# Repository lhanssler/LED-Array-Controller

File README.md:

**LED-Array-Controller**

**Part A: Repository Contents**
1. telemetrix_controller.py: Python module created to interact with the Arduino
    Nano. Allows the Nano to connect to a PCA9685 driver and flash LEDs.
    This module is the only required import. Other files are dependencies.
2. telemetrix: Python package which can be imported to control an Arduino
    using Python over a serial connection. This package is a dependency of
    telemetrix_controller.py and telemetrix_pca9685.
3. telemetrix_pca9685: Python package which can be imported to connect with an
    Arduino and PCA9685 driver. The package uses telemetrix for the Arduino
    connection and is a dependency of telemetrix_controller.py. The package
    was sourced from: https://github.com/MrYsLab/telemetrix-extensions
4. Telemetrix4Arduino: Folder containing Telemetrix4Arduino.ino, the Arduino
    sketch file which must be opened in the Arduino IDE and uploaded to the
    Arduino Nano before the connection from Python is established. ino files
    can only be opened in the Arduino IDE if they are located in a folder
    of the same name, which is why the folder is provided.
5. warm_test.txt: A text file is used to configure the LED array controller
    when the telemetrix_controller.py module is utilized. This is the text
    file used for the January 2025 warm test in the LL130 cryostat and can be
    referenced as an example. The file is explained in more detail in Part C of
    the README.md.
6. serial: Python's serial library, a dependency of telemetrix. serial is
    should already be installed on the host device, but some devices running
    older versions of Python have issues when telemetrix calls certain functions
    from serial. This version of serial has been shown to function properly.
7. KiCad Files: Folder containing the KiCad files for LED Array Controller PCBs.
    Revisions 3 and 4 of the board are in the folder, which includes their
    schematics and board diagrams. KiCad Files has its own README file in
    the folder.
8. README.md: This README file.

**Part B: Repository Dependencies**
1. Arduino IDE: Download at this link: https://www.arduino.cc/en/software
2. Telemetrix4Arduino: Arduino library. Download instructions:
    In the Arduino IDE, select Tools -> Manage Libraries and search for
    Telemetrix4Arduino. Install the library and its dependencies.
3. Telemetrix4Arduino.ino, Arduino sketch: File to be uploaded to the Arduino
    Nano to begin the serial connection. This is the Telemetrix4Arduino library
    example file.
4. telemetrix, telemetrix_pca9685, serial: Python packages included in this
    repository which are dependencies of the telemetrix_controller.py file.
5. Configuration text file: The text file which defines the LED Array PCB's
    connection to the LED Array Controller PCB.

**Part C: Instructions for Using telemetrix_controller**
1. Create the configuration file: This is the text file, with warm_test.txt as
    an example. Each row represents an Arduino Nano pin or PCA9685 driver
    channel to be used for the LED array. Each row has 3 columns delimited by a
    single space. The first column is the row or column number (1-indexed) of
    the LED array which the pin/channel corresponds to. The second column is
    the digital pin or channel number. The third number is the driver address.
    If the text row corresponds to a Nano pin, then the driver address should
    be entered as 0. The default driver address is 64 (or 0x40), which
    corresponds to none of the solder jumpers being connected on the LED Array
    Controller PCB.
2. In the Arduino IDE, upload the Telemetrix4Arduino.ino file to the Arduino
    Nano.
3. In Python, import telemetrix_controller. No other explicit imports are
    required for repository use.
4. In Python, create an object from the telemetrix_controller.Arduino class. The
    constructor only has one argument, which is required: the string indicating
    the filepath to the configuration file.
5. The object's methods can now be called to control the LED array.
    Please refer to the docstrings in telemetrix_controller.py for further
    instructions on use.

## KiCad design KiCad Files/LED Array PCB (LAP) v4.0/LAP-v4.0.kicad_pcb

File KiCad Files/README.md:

**KiCad Files**

The KiCad Files folder contains the two most recent revisions of the LED Array
PCB (LAP): v3.0 and v4.0.

The telemetrix_controller module was designed with v3.0 in mind, and v3.0 is
the version that is printed and populated in LL113. v3.0 contains:
- An Arduino Nano (used with header pins), PCA9685 IC which is SMT soldered
    directly to the board.
- A through-hole D-sub 37 connector to connect to the LED array in the
    cryostat.
- Through-hole resistors for each anode.
- Through-holes which can be used to add capacitors to GND in parallel with
    the LED array anodes.
- Unconnected solder jumpers which can be used to assign an address to
    the board's PCA9685.
- Two through-hole connections each for VCC, GND, OE, SDA, and SCL lines,
    which allow multiple copies of the PCB to be daisy-chained for using
    multiple drivers (this requires each board to have a different address,
    as indicated through connecting solder jumpers).
- Pulldown resistors and an indicator LED.

There is one potential issue with v3.0: the RX and TX pins on the Arduino Nano
are routed to the D-sub 37 connector, which implies that they can be used as
cathodes. This is not possible, as these are the RX and TX lines that are used
by the USB connection between the Arduino and host device, so they cannot be
used for the LED array.
Issues can be avoided by simply not connecting these D-sub 37 connector pins to
the LED array. v4.0 avoids any confusion by not routing the TX or RX pins to the
D-sub 37 connector. In addition to the TX and RX routing improvement, v4.0 also
uses SMT resistors instead of through-hole resistors, resulting in a reduced PCB
size. v3.0 and v4.0 are otherwise the same.

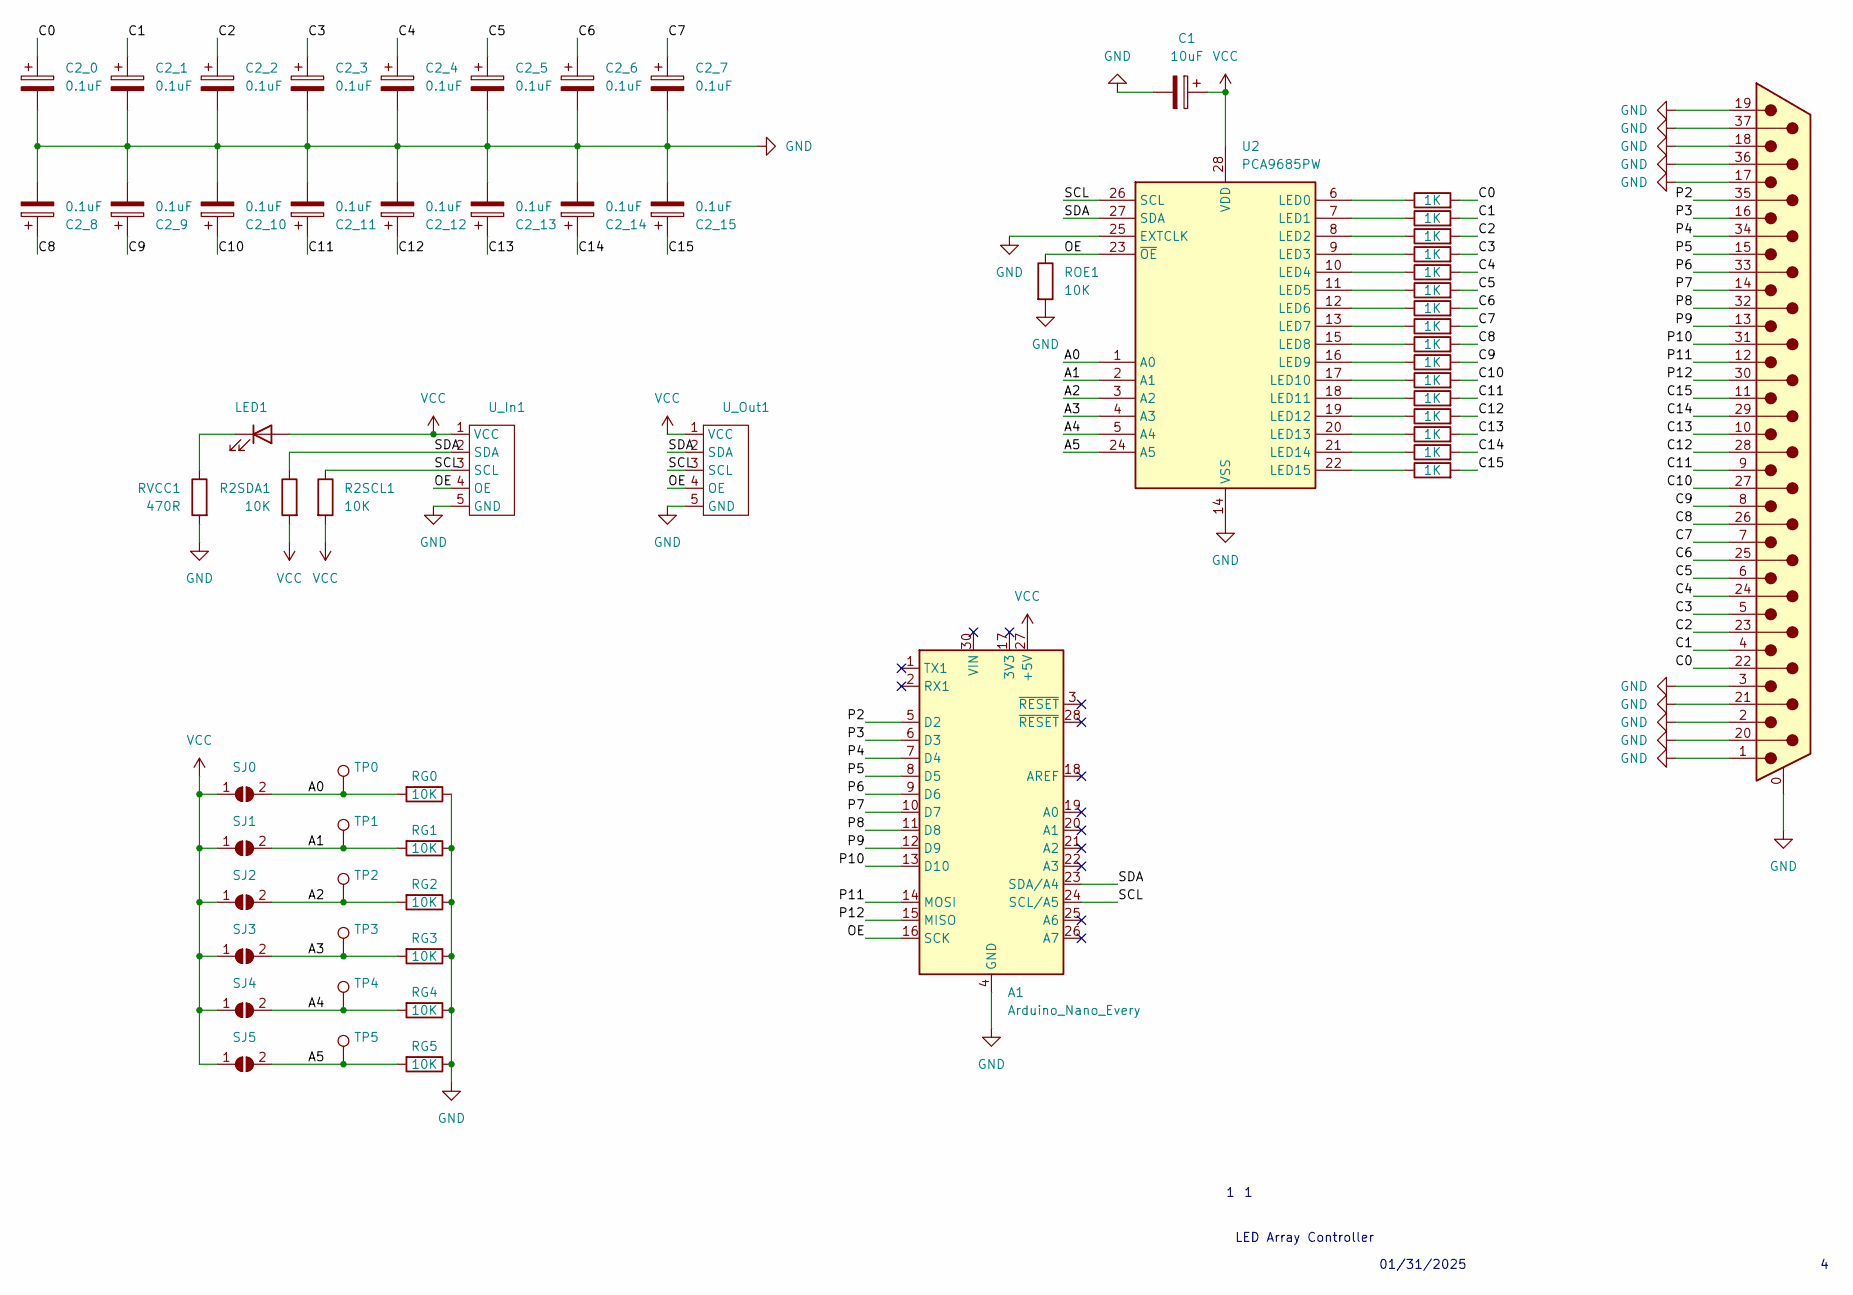
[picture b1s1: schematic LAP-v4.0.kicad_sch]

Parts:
A1: Arduino_Nano_Every; Arduino_Nano
C1: 10uF; CP_Radial_D8.0mm_P2.50mm
C2_0, C2_1, C2_2, C2_3, C2_4, C2_5, C2_6, C2_7, C2_8, C2_9, C2_10, C2_11, C2_12, C2_13, C2_14, C2_15: 0.1uF; CP_Radial_D8.0mm_P2.50mm
J1: DC37_Plug_MountingHoles; DSUB-37_Male_Horizontal_P2.77x2.84mm_EdgePinOffset4.94mm_Ho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
LED1: LED; LED_0805_2012Metric
R0, R1, R2, R3, R4, R5, R6, R7, R8, R9, R10, R11, R12, R13, R14, R15: 1K; R_0603_1608Metric
R2SCL1, R2SDA1: 10K; R_0603_1608Metric
RG0, RG1, RG2, RG3, RG4, RG5: 10K; R_0603_1608Metric
ROE1: 10K; R_0603_1608Metric
RVCC1: 470R; R_0603_1608Metric
SJ0, SJ1, SJ2, SJ3, SJ4, SJ5: SolderJumper_2_Open; SolderJumper-2_P1.3mm_Open_RoundedPad1.0x1.5mm
TP0, TP1, TP2, TP3, TP4, TP5: TestPoint; TestPoint_THTPad_1.5x1.5mm_Drill0.7mm
U2: PCA9685PW; TSSOP-28_4.4x9.7mm_P0.65mm
U_In1: Board_Connector
U_Out1: Board_Connector

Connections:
/A0: RG0.2, SJ0.2 (B), TP0.1, U2.1 (A0)
/A1: RG1.2, SJ1.2 (B), TP1.1, U2.2 (A1)
/A2: RG2.2, SJ2.2 (B), TP2.1, U2.3 (A2)
/A3: RG3.2, SJ3.2 (B), TP3.1, U2.4 (A3)
/A4: RG4.2, SJ4.2 (B), TP4.1, U2.5 (A4)
/A5: RG5.2, SJ5.2 (B), TP5.1, U2.24 (A5)
/C0: C2_0.1, J1.22, R0.2
/C1: C2_1.1, J1.4, R1.2
/C2: C2_2.1, J1.23, R2.2
/C3: C2_3.1, J1.5, R3.2
/C4: C2_4.1, J1.24, R4.2
/C5: C2_5.1, J1.6, R5.2
/C6: C2_6.1, J1.25, R6.2
/C7: C2_7.1, J1.7, R7.2
/C8: C2_8.1, J1.26, R8.2
/C9: C2_9.1, J1.8, R9.2
/C10: C2_10.1, J1.27, R10.2
/C11: C2_11.1, J1.9, R11.2
/C12: C2_12.1, J1.28, R12.2
/C13: C2_13.1, J1.10, R13.2
/C14: C2_14.1, J1.29, R14.2
/C15: C2_15.1, J1.11, R15.2
/OE: A1.16 (SCK), ROE1.1, U2.23 (~OE), U_In1.4 (OE), U_Out1.4 (OE)
/P2: A1.5 (D2), J1.35
/P3: A1.6 (D3), J1.16
/P4: A1.7 (D4), J1.34
/P5: A1.8 (D5), J1.15
/P6: A1.9 (D6), J1.33
/P7: A1.10 (D7), J1.14
/P8: A1.11 (D8), J1.32
/P9: A1.12 (D9), J1.13
/P10: A1.13 (D10), J1.31
/P11: A1.14 (MOSI), J1.12
/P12: A1.15 (MISO), J1.30
/SCL: A1.24 (SCL/A5), R2SCL1.1, U2.26 (SCL), U_In1.3 (SCL), U_Out1.3 (SCL)
/SDA: A1.23 (SDA/A4), R2SDA1.1, U2.27 (SDA), U_In1.2 (SDA), U_Out1.2 (SDA)
GND: A1.4 (GND), A1.29 (GND), C1.2, C2_0.2, C2_1.2, C2_2.2, C2_3.2, C2_4.2, C2_5.2, C2_6.2, C2_7.2, C2_8.2, C2_9.2, C2_10.2, C2_11.2, C2_12.2, C2_13.2, C2_14.2, C2_15.2, J1.0 (PAD), J1.1, J1.2, J1.3, J1.17, J1.18, J1.19, J1.20, J1.21, J1.36, J1.37, RG0.1, RG1.1, RG2.1, RG3.1, RG4.1, RG5.1, ROE1.2, RVCC1.2, U2.14 (VSS), U2.25 (EXTCLK), U_In1.5 (GND), U_Out1.5 (GND)
unnamed: LED1.1 (K), RVCC1.1
unnamed: R0.1, U2.6 (LED0)
unnamed: R1.1, U2.7 (LED1)
unnamed: R2.1, U2.8 (LED2)
unnamed: R3.1, U2.9 (LED3)
unnamed: R4.1, U2.10 (LED4)
unnamed: R5.1, U2.11 (LED5)
unnamed: R6.1, U2.12 (LED6)
unnamed: R7.1, U2.13 (LED7)
unnamed: R8.1, U2.15 (LED8)
unnamed: R9.1, U2.16 (LED9)
unnamed: R10.1, U2.17 (LED10)
unnamed: R11.1, U2.18 (LED11)
unnamed: R12.1, U2.19 (LED12)
unnamed: R13.1, U2.20 (LED13)
unnamed: R14.1, U2.21 (LED14)
unnamed: R15.1, U2.22 (LED15)
VCC: A1.27 (+5V), C1.1, LED1.2 (A), R2SCL1.2, R2SDA1.2, SJ0.1 (A), SJ1.1 (A), SJ2.1 (A), SJ3.1 (A), SJ4.1 (A), SJ5.1 (A), U2.28 (VDD), U_In1.1 (VCC), U_Out1.1 (VCC)

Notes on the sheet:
01/31/2025
LED Array Controller

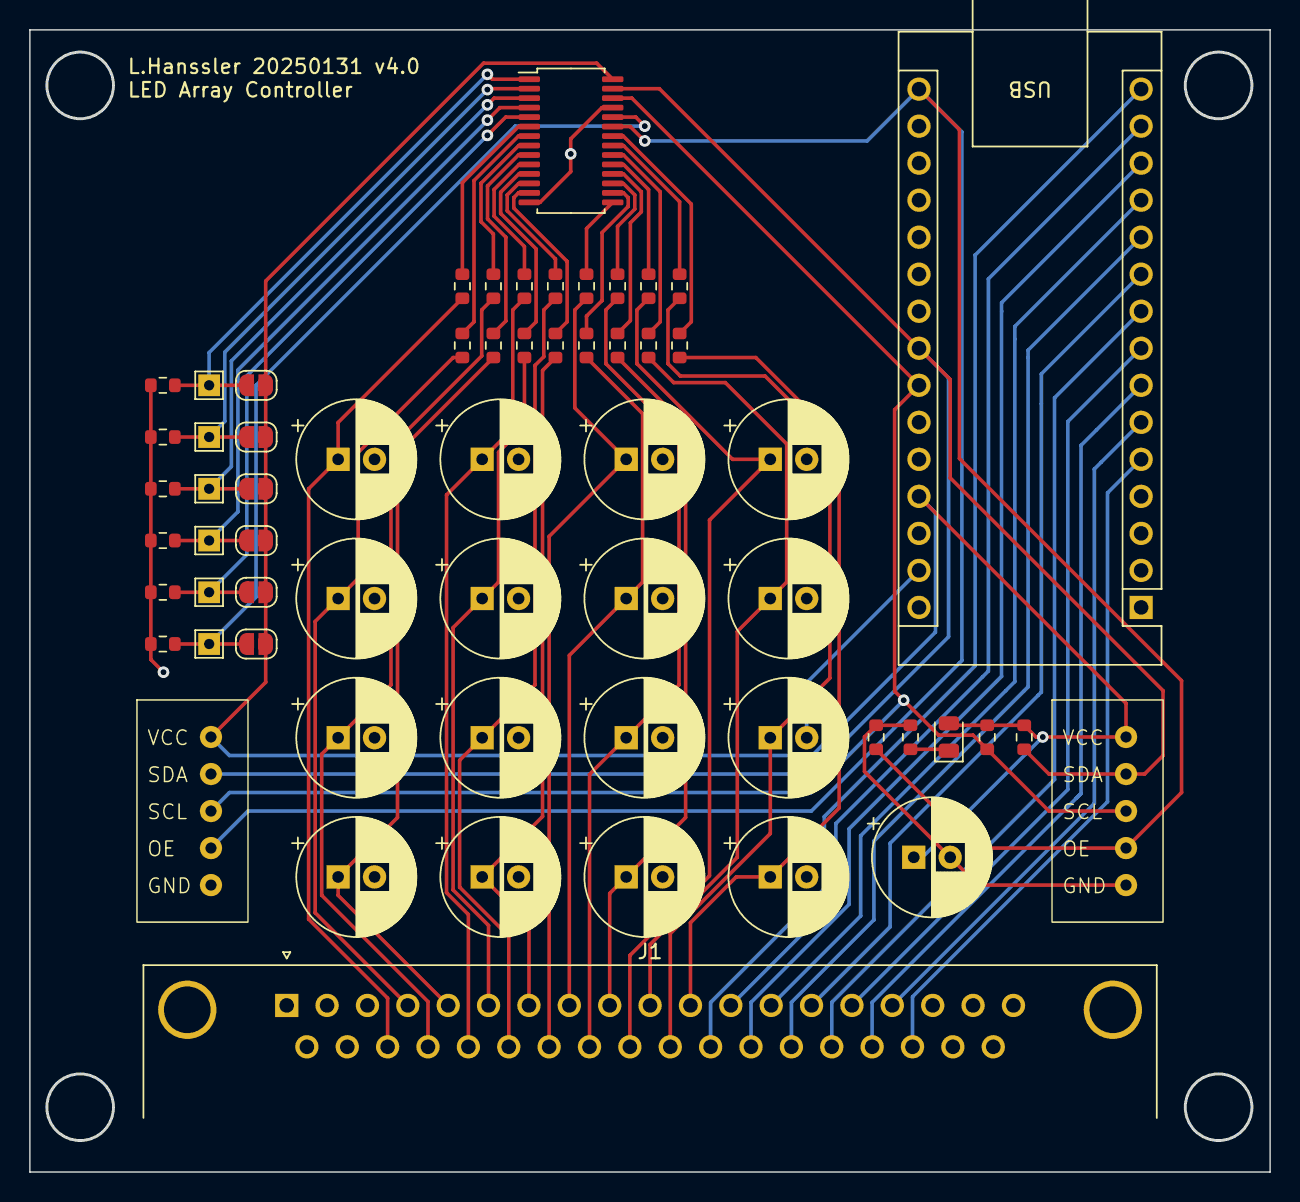
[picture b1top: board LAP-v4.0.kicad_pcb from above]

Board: 2 copper layers, 85.0 x 78.3 mm, 61 parts (0 on the bottom side), 55 nets.

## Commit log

2024-09-11 Rename telemetrix_config.txt to ExampleConfig.txt
2024-09-13 Rename Nano-Driver.kicad_sch to KiCad_Board.kicad_sch
2024-09-13 Rename Nano-Driver.kicad_pcb to KiCad_Board.kicad_pcb
2024-09-13 Rename Nano-Driver.kicad_pro to KiCad_Board.kicad_pro
2024-11-30 Update and rename TelemetrixController.py to PythonCode/TelemetrixController.py
    Updated comment, moved code into a code folder
2024-11-30 Rename ExampleConfig.txt to PythonCode/ExampleConfig.txt
    Moved to Python Code directory
2024-11-30 Rename PythonCode/ExampleConfig.txt to ExampleConfig.txt
    Removed from code directory
2024-11-30 Rename PythonCode/TelemetrixController.py to telemetrix_controller.py
    Removed from code directory; renamed in snake case
2024-11-30 Rename ExampleConfig.txt to example_config.txt
    Renamed in snake case
2024-11-30 Delete KiCad_Board directory
    Deleted KiCad files
2024-11-30 Create README.md
    Added an explanation for installing dependencies and running code for the library
2024-11-30 Update README.md
    Added that the Telemetrix4Arduino Arduino library should be installed with dependencies
2024-12-01 Update README.md
    Added the point when extra files may be deleted, changed pull to clone
2024-12-01 Update README.md
    Changed and bolded the readme title
2025-01-24 Updated KiCad Files and added KiCad Files README.md. Added serial package from my Macbook which has been shown to work for the module.
2025-01-26 Test commit
2025-01-26 Undo test commit
2025-01-26 Delete KiCad Files/.DS_Store
    Delete DS_Store file
2025-01-26 Replaced example config file with config file used for Jan 2025 warm test
2025-01-26 Fixed bullet list formatting
2025-01-26 Delete KiCad Files/LED Array PCB (LAP) v4.0/.DS_Store
    Deleted DS_Store file
2025-01-26 Delete KiCad Files/LED Array PCB (LAP) v3.0/.DS_Store
    Deleted DS_Store file
2025-01-26 Delete telemetrix/__pycache__ directory
    Deleted pycache
2025-01-26 Delete telemetrix_pca9685/__pycache__ directory
    Deleted pycache
2025-01-26 Delete serial/__pycache__ directory
    Deleted pycache
2025-01-26 Added title line
2025-01-26 removed line breaks
2025-01-26 Updated README draft; not yet completed
2025-01-29 Updated README file to have more explicit instructions and complete explanations.
2025-01-29 Cleaned up module formatting.
2025-01-29 Fixed module formatting and removed unused variables
2025-01-29 Added Telemetrix4Arduino example sketch
2025-01-29 Updated the README following the addition of the ino file
2025-01-29 Connected GND through-holes in LAP v4.0 to fix DRC error
2025-01-31 Finalized PCBs
